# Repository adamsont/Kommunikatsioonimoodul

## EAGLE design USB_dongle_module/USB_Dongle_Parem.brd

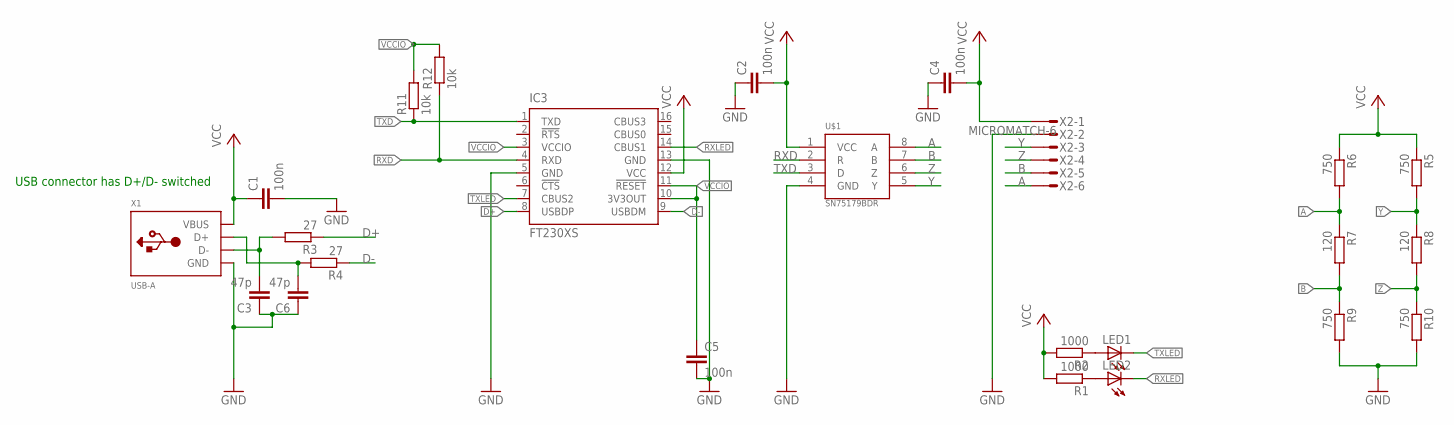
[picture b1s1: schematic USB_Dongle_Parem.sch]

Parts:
C1, C2, C4, C5: 100n; C0603
C3, C6: 47p; C0603
IC3: FT230XS; SSOP16
LED1, LED2: LED_ESML0603; LED_SML0603
R1, R2: 1000; R0603
R3, R4: 27; R0603
R5, R6, R9, R10: 750; R0603
R7, R8: 120; R0603
R11, R12: 10k; R0603
U$1: SN75179BDR; SOIC8
X1: USB-A; MOLEX_480371000
X2: MICROMATCH-6

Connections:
A: R6.2, R7.1, U$1.8 (A), X2.6
B: R7.2, R9.1, U$1.7 (B), X2.5
D+: IC3.8 (USBDP), R3.1
D-: IC3.9 (USBDM), R4.1
GND: C1.2, C2.1, C3.1, C4.1, C5.2, C6.1, IC3.5 (GND), IC3.13 (GND), R9.2, R10.2, U$1.4 (GND), X1.4 (GND), X2.2
unnamed: LED2.A, R1.1
unnamed: LED1.A, R2.1
RXD: IC3.4 (RXD), R12.1, U$1.2 (R)
RXLED: IC3.14 (CBUS1), LED2.C
SA: C3.2, R3.2, X1.2 (D-)
SAD: C6.2, R4.2, X1.3 (D+)
TXD: IC3.1 (TXD), R11.1, U$1.3 (D)
TXLED: IC3.7 (CBUS2), LED1.C
VCC: C1.1, C2.2, C4.2, IC3.12 (VCC), R1.2, R2.2, R5.1, R6.1, U$1.1 (VCC), X1.1 (VBUS), X2.1
VCCIO: C5.1, IC3.3 (VCCIO), IC3.10 (3V3OUT), IC3.11 (!RESET), R11.2, R12.2
Y: R5.2, R8.1, U$1.5 (Y), X2.3
Z: R8.2, R10.1, U$1.6 (Z), X2.4

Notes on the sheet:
USB connector has D+/D- switched

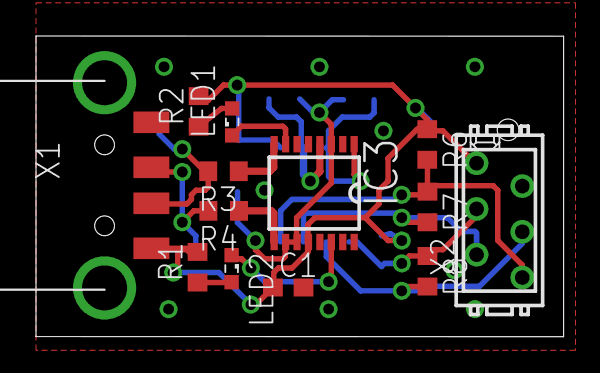
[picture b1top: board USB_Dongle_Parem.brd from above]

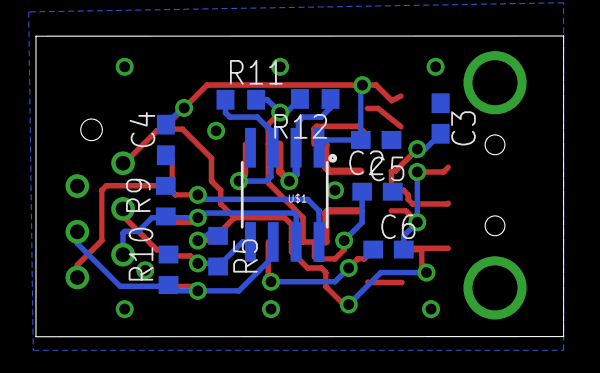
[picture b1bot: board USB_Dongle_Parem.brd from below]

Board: 2 copper layers, 29.3 x 16.7 mm, 24 parts (11 on the bottom side), 17 nets.

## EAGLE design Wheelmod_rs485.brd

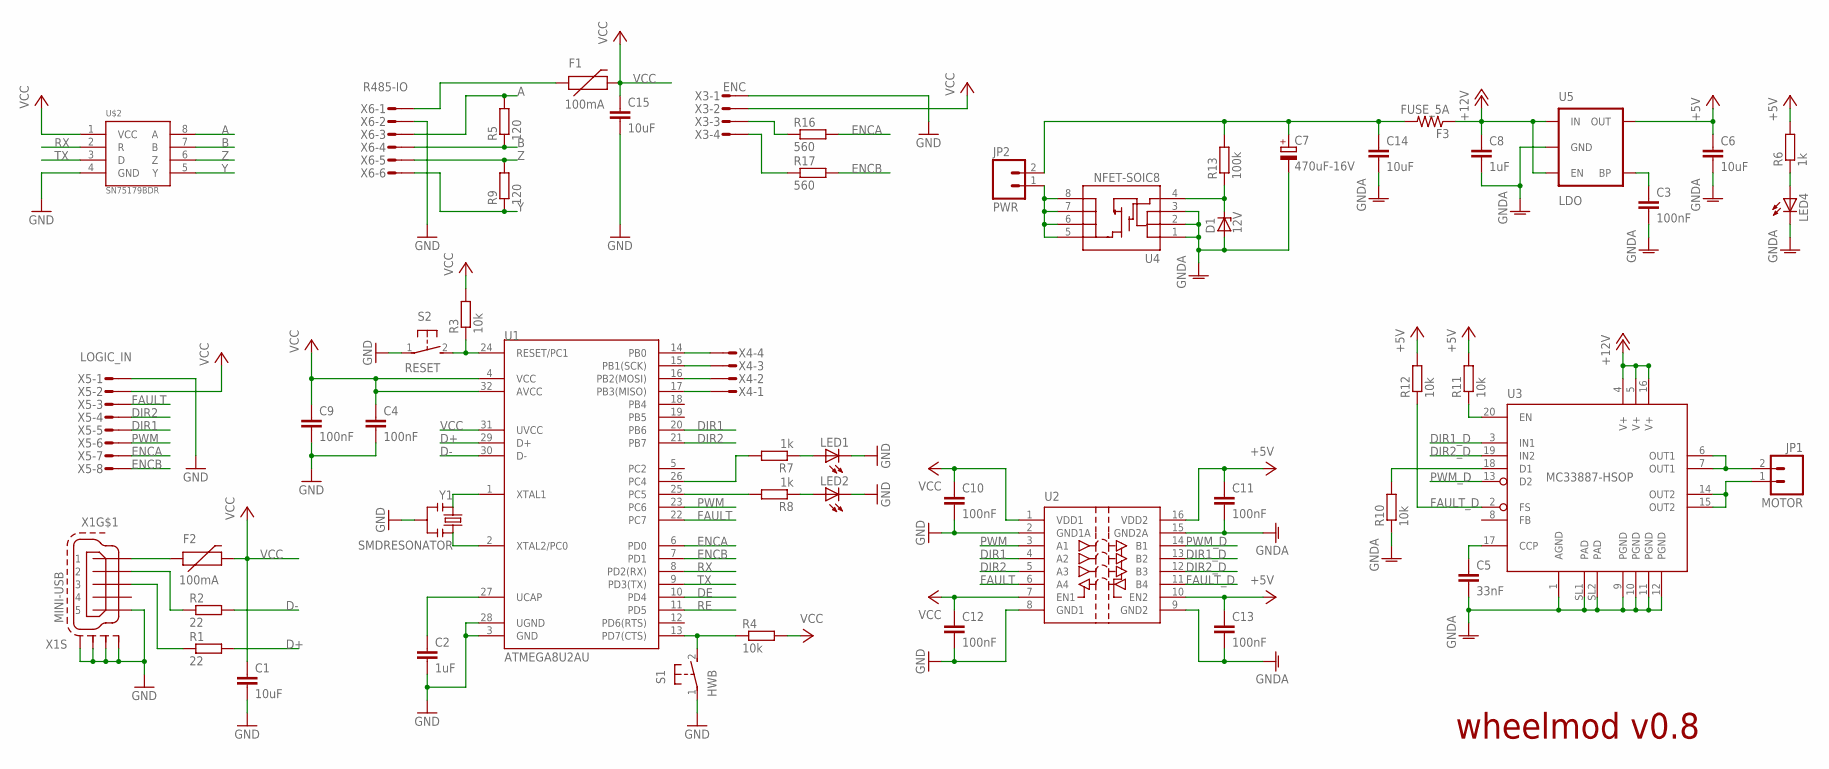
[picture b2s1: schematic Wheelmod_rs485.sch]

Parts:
C1, C6, C14, C15: 10uF; C1206K
C2, C8: 1uF; C0603K
C3, C4, C9, C10, C11, C12, C13: 100nF; C0603K
C5: 33nF; C0603K
C7: 470uF-16V; E3,5-8
D1: 12V; SOD123
F1, F2: 100mA; PTC-1206
F3: FUSE_5A; R1206
JP1: MOTOR; SCREWTERMINAL-3.5MM-2
JP2: PWR; SCREWTERMINAL-3.5MM-2
LED1, LED2, LED4: LEDCHIP-LED0603; CHIP-LED0603
R1, R2: 22; R0603
R3, R4, R10, R11, R12: 10k; R0603
R5, R9: 120; R0603
R6, R7, R8: 1k; R0603
R13: 100k; R0603
R16, R17: 560; R0603
S1: HWB; ADTSM3
S2: RESET; ADTSM3
U1: ATMEGA8U2AU; TQFP32-08
U2: SI8441IS1; SO16
U3: MC33887-HSOP; HSOP
U4: NFET-SOIC8; SO08
U5: LDO; SOT23-5
U$2: SN75179BDR; SOIC8
X1: MINI-USB; 32005-301
X3: ENC; MICROMATCH-4
X4: MICROMATCH-4
X5: LOGIC_IN; MICROMATCH-8
X6: R485-IO; MICROMATCH-6
Y1: SMDRESONATOR; PBRC-M

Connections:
+5V: C6.1, C11.1, C13.1, R6.2, R11.2, R12.2, U2.10 (EN2), U2.16 (VDD2), U5.5 (OUT)
+12V: C8.1, F3.1, U3.4 (V+), U3.5 (V+), U3.16 (V+), U5.1 (IN), U5.3 (EN)
A: R5.2, U$2.8 (A), X6.3
B: R5.1, U$2.7 (B), X6.4
D+: R1.2, U1.29 (D+)
D-: R2.2, U1.30 (D-)
DE: U1.10 (PD4)
DIR1: U1.20 (PB6), U2.4 (A2), X5.5
DIR1_D: U2.13 (B2), U3.3 (IN1)
DIR2: U1.21 (PB7), U2.5 (A3), X5.4
DIR2_D: U2.12 (B3), U3.19 (IN2)
ENCA: R16.2, U1.6 (PD0), X5.7
ENCB: R17.2, U1.7 (PD1), X5.8
FAULT: U1.22 (PC7), U2.6 (A4), X5.3
FAULT_D: R12.1, U2.11 (B4), U3.2 (FS)
GND: C1.2, C2.2, C4.2, C9.2, C10.2, C12.2, C15.2, LED1.C, LED2.C, S1.1, S2.1, U1.3 (GND), U1.28 (UGND), U2.2 (GND1A), U2.8 (GND1), U$2.4 (GND), X1.5, X1.M1 (S1), X1.M2 (S2), X1.M3 (S3), X1.M4 (S4), X3.1, X5.1, X6.2, Y1.2
GNDA: C3.2, C5.2, C6.2, C7.-, C8.2, C11.2, C13.2, C14.2, D1.A, LED4.C, R10.1, U2.9 (GND2), U2.15 (GND2A), U3.1 (AGND), U3.9 (PGND), U3.10 (PGND), U3.11 (PGND), U3.12 (PGND), U3.SL1 (PAD), U3.SL2 (PAD), U4.1 (S), U4.2 (S), U4.3 (S), U5.2 (GND)
unnamed: C2.1, U1.27 (UCAP)
unnamed: R4.1, S1.2, U1.13 (PD7(CTS))
unnamed: LED1.A, R7.1
unnamed: LED2.A, R8.1
unnamed: R1.1, X1.3
unnamed: F2.1, X1.1
unnamed: R2.1, X1.2
unnamed: U1.1 (XTAL1), Y1.1
unnamed: U1.2 (XTAL2/PC0), Y1.3
unnamed: R3.1, S2.2, U1.24 (RESET/PC1)
unnamed: C3.1, U5.4 (BP)
unnamed: R8.2, U1.25 (PC5)
unnamed: LED4.A, R6.1
unnamed: C5.1, U3.17 (CCP)
unnamed: R11.1, U3.20 (EN)
unnamed: R10.2, U3.18 (D1)
unnamed: R7.2, U1.26 (PC4)
unnamed: D1.C, R13.1, U4.4 (G)
unnamed: JP2.1, U4.5 (D), U4.6 (D), U4.7 (D), U4.8 (D)
unnamed: JP1.2, U3.6 (OUT1), U3.7 (OUT1)
unnamed: U1.14 (PB0), X4.4
unnamed: JP1.1, U3.14 (OUT2), U3.15 (OUT2)
unnamed: U1.15 (PB1(SCK)), X4.3
unnamed: U1.16 (PB2(MOSI)), X4.2
unnamed: R16.1, X3.3
unnamed: R17.1, X3.4
unnamed: C7.+, C14.1, F3.2, JP2.2, R13.2
unnamed: U1.17 (PB3(MISO)), X4.1
unnamed: F1.1, X6.1
PWM: U1.23 (PC6), U2.3 (A1), X5.6
PWM_D: U2.14 (B1), U3.13 (D2)
RE: U1.11 (PD5)
RX: U1.8 (PD2(RX)), U$2.2 (R)
TX: U1.9 (PD3(TX)), U$2.3 (D)
VCC: C1.1, C4.1, C9.1, C10.1, C12.1, C15.1, F1.2, F2.2, R3.2, R4.2, U1.4 (VCC), U1.31 (UVCC), U1.32 (AVCC), U2.1 (VDD1), U2.7 (EN1), U$2.1 (VCC), X3.2, X5.2
Y: R9.1, U$2.5 (Y), X6.6
Z: R9.2, U$2.6 (Z), X6.5

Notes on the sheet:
wheelmod v0.8

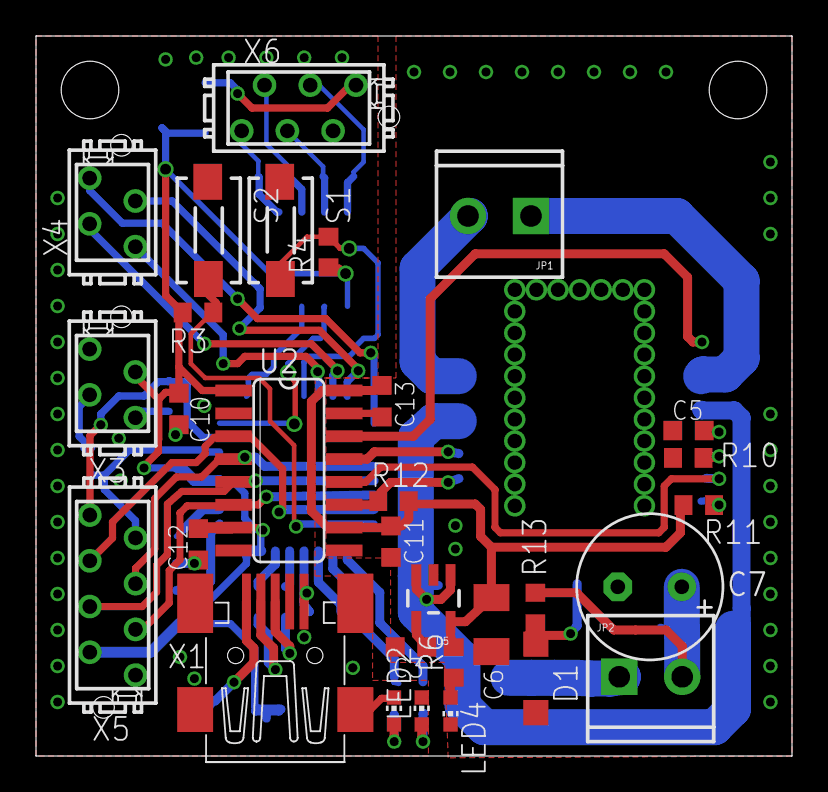
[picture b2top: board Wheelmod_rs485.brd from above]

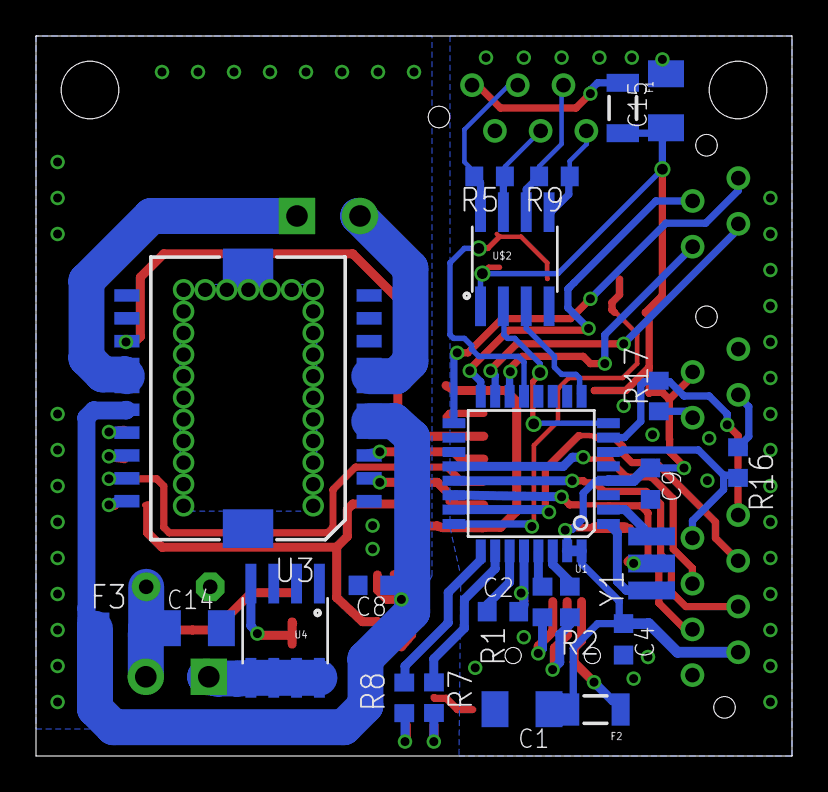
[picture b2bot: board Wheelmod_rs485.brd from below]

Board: 2 copper layers, 42.0 x 40.0 mm, 53 parts (23 on the bottom side), 52 nets.

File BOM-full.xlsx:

Nimi | Tähis | Mouser | Farnell | Kogus
100k 0603 | R13 |  |  | 1
100nF 0603 | C3, C4, C9, C10, C11, C12, C13 |  |  | 7
10k 0603 | R3, R4, R10, R11, R12 |  |  | 5
10uF 1206 | C1, C6, C14, C15 |  |  | 4
120R 0603 | R5, R9 |  |  | 2
12V zener SOD123 | D1 | 78-MMSZ4699-V |  | 1
1k 0603 | R6, R7, R8 |  |  | 3
1uF 0603 | C2, C8 |  |  | 2
22R 0603 | R1, R2 |  |  | 2
33nF 0603 | C5 |  |  | 1
470uF 25V | C7 |  | 1219470 | 1
560R 0603 | R16, R17 |  |  | 2
5V LDO SOT23 | U5 |  | 2100328 | 1
ATMEGA32U2 TQFP32 | U1 |  | 1748524 | 1
Fuse 5A 1206 | F3 | 637-F1206SB5000V032 | 1832091 | 1
LED 0603 | LED1, LED2, LED4 |  |  | 3
MC33887-HSOP | U3 | 841-MC33886PVW |  | 1
MICROMATCH-4 | X3, X4 |  |  | 2
MICROMATCH-6 | X6 |  | 148519 | 1
MICROMATCH-8 | X5 |  |  | 1
MINI-USB-SCHIELD-32005-301 | X1 | 154-15320-E | 1125348 | 1
MOSFET-NCHANNEL-SOIC8 | U4 | 621-DMS3015SSS-13 | 1863728 | 1
PTC 100mA 1206 | F1, F2 |  | 1800751 | 2
Screw terminal M023.5MM | JP1, JP2 | 538-39357-0002 | 3882615 | 2
SI8441IS1 SO16 | U2 | 634-SI8441AA-D-IS1 |  | 1
SMDRESONATOR45X20 PBRC-M | Y1 | 581-PBRC16.00MR70X | 2101363 | 1
SN75179BDR SOIC8 | U$2 |  | 2437313 | 1
Tactale switch ADTSM3 | S1, S2 | 642-ADTSM32RVTR |  | 1
Micromatch-4 plug |  |  | 149032 | 2
Micromatch-6 plug |  |  | 149068 | 1

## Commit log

2015-08-24 Added fixes to Tiina's version
2015-08-24 Changing RS485 IC
2015-08-25 Rerouted USB dongle
2015-08-25 Fixed AB-YZ GND-VCC bugs
2015-08-25 USB D+/D- fixes
2015-09-14 Added BOM

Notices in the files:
parts and their libraries:
SparkFun-DigitalIC: Licensing: Creative Commons ShareAlike 4.0 International - https://creativecommons.org/licenses/by-sa/4.0
SparkFun: Licensing: CC v3.0 Share-Alike You are welcome to use this library for commercial purposes.
